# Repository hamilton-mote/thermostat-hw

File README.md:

# Hamilton open-source thermostat

The Hamilton thermostat is an open-source single stage thermostat built around the [Hamilton](https://github.com/hamilton-mote/hw) and [Nucleum](https://github.com/lab11/nucleum) motes. The core motivation of the project is to integrate the hardware necessary to turn these low-cost and low-power motes into an energy efficient and feature-rich thermostat.

The Hamilton thermostat can control a standard single stage heating and/or cooling system with a circular fan (R/Rh/Rc, W, Y, and G wires). The design features a temperature sensor (AT30TS74), humidity/temperature sensor (HDC1080), PIR sensor (EKMB1101111), real-time clock (MCP7940N), and 1Mbit EEPROM (AT24CM01). Wireless communication is achieved via the 802.15.4 radio (built into the SAMR21 of the Hamilton mote) or the Bluetooth Low Energy (BLE) radio (built into the NRF51822 of the Nucleum mote). The thermostat can be powered by 3 AA batteries or by 24VAC power (requires a C wire). The design also includes a simple user interface with 4 buttons and LED-based temperature and setting indication. The user interface can easily be replaced with a custom board by connecting to the main thermostat board via pinouts for the I2C bus, power (+3V3/GND), 2 analog pins, and 4 digital pins.

### Parts Overview

* AT30TS74 (I2C Address 1001000): The AT30TS74 temperature sensor has a configurable resolution of 9 to 12 bits and a typical accuracy of +/- 1 degree Celsius.
* HDC1080 (I2C Address 1000000): The HDC1080 humidity and temperature sensor has a configurable resolution of 8, 11, or 14 bits for humidity and 11 or 14 bit for temperature. The typical accuracy for humidity and temperature is +/- 2% and +/- 0.2 degree Celsius, respectively.
* MCP7940N (I2C Address 1101111): The MCP7940N is a real-time clock/calendar with SRAM.
* AT24CM02 (I2C Address 10100###): The AT24CM02 provides 2-Mbits (256-Kbytes) of Serial EEPROM. (Note: The original version of the Hamilton thermostat included AT24CM01 chips)
* PCA9557 (I2C Address 0011000): The PCA9557 is an 8 channel I/O parallel port expander. The expander is used to control the 3 latching relays (EE2-3TNUH-L) which actuate the heating system, cooling system, and circular fan.
* TLC59116 (I2C Addresses 1100001, 1100011, and 1100111): The TLC59116 is a 16 channel constant-current LED sink driver with 256-step (8-bit) linear programmable brightness. The Hamilton thermostat interface board includes 3 TLC59116 chips.
* EKMB1101111: The EKMB1101111 is a fully integrated PIR motion sensor with 1µA low current consumption. The output of the PIR sensor is connected to pin PA06 of the SAMR21 chip and P05/AIN6 of the NRF51822 chip.

### Communication

Communication between the SAMR21 chip or the NRF51822 chip and the other components of the Hamilton thermostat is primarily achieved via the shared I2C bus. The SAMR21 chip is connected to the bus with pin PA16 as SDA and PA17 as SCL and the NRF51822 chip is connected with pin P07 as SDA and P01 as SCL. The I2C addresses of the components are noted in the list above.

Communication between the SAMR21 chip and the NRF51822 chip is achieved over an SPI link. The SAMR21 chip is design to use SERCOM2 with PA08/PAD[0] as MOSI, PA09/PAD[1] as MISO,
PA15/PAD[3] as SCK, and PA14/PAD[2] as chip select.  The NRF51822 chip provides flexibility in the assignment of SPI pins and is designed to use P30 as MOSI, P29 as MISO, P00 as SCK, and P28 as chip select.

Additionally, the SAMR21 and NRF51822 chips are connected by several additional traces.
* A6 (the PIR sensor output) to SAMR21 pin PA06 and NRF51822 pin P05/AIN6.
* A7 to SAMR21 pin PA07 and NRF51822 pin P06/AIN7.
* D18 to SAMR21 pin PA18 and NRF51822 pin P18.
* D19 to SAMR21 pin PA19 and NRF51822 pin P19. There is also an LED connected to D19.
* D24 to SAMR21 pin PA24 and NRF51822 pin P25.
* D25 to SAMR21 pin PA25 and NRF51822 pin P25.
If necessary, these traces can be physically cut on the bottom on the Hamilton thermostat main board to sever the connections to the NRF51822 chip.

Lastly, the Hamilton thermostat is capable of wireless communication via the 802.15.4 radio (built into the SAMR21 chip) and the BLE radio (built into the NRF51822 chip).

### Relays

The Hamilton thermostat main board includes 3 EE2-3TNUH-L dual-coil latching signal relays for actuating a heating system (W wire), cooling system (Y wire), and circular fan (G wire).  Each relay is rated for a coil voltage of 3VDC, a contact current of 2A, and a switching voltage of up to 250VAC. Because the EE2-3TNUH-L is a latching relay, it maintains the contact position indefinitely without requiring a current to be applied. Thus, each relay contains 2 coils (1 for setting and 1 for releasing) and a current pulse is applied to either coil to change the contact position. Note that applying a current to one of the coils over a long period of time will damage the relay.

Each relay is connected to either the W wire (heat), Y wire (cooling), or G wire (fan). Setting a relay will connect the respective wire to the R/Rh/Rc wire and releasing the relay will sever the connection. The relays are controlled via the PCA9557 8 channel I/O expander. The W relay is connected to IO0 for setting and IO1 for releasing, the Y relay to IO2 for setting and IO3 for releasing, and the G relay to IO4 for setting and IO5 for releasing.

Lastly, the Hamilton thermostat is capable of simultaneously connecting the G wire (fan) when the W relay or Y relay is set. Adding the R18 jumper will cause the W relay to connect both the W and G wires to R when the relay is set and adding the R17 jumper will cause the Y relay to connect the Y and G relays to R.

### Power

The Hamilton thermostat can be power by battery and/or 24VAC power (if a C wire is available). The Hamilton thermostat main board includes a 3 AA battery holder and a AP2210 3.3VDC 300mA LDO regulator. If necessary, regulator can be bypassed by adding the R1 jumper.

If a C wire is available, the thermostat can operate on 24VAC power. For AC/DC conversion, the main board includes a full wave bridge rectifier and an OKI-78SR 36VDC to 3.3VDC 1.5A buck converter. The thermostat is designed to allow for operation on 24VAC power with battery backup.

### User Interface

The Hamilton thermostat has a simple and intuitive user interface for communicating the current temperature measurement and set point and for enabling a user to perform basic operations like setting the mode (heating, cooling, off) and adjusting the set point. The interface board includes four buttons: one for setting the mode, two for adjusting the temperature set point, and one for setting a temporary temperature hold.

The board also includes 40 LEDs for denoting the thermostats settings. To communicate the current temperature measurement and set point, 32 of the LEDs are arranged in an arc around the center of the board (16 for the measurement and 16 for the set point). The LEDs are controlled via three TLC59116 16 channel LED sink drivers.

The interface board is connected to the main thermostat board via pinouts for the I2C bus (SDA and SCL), power (+3.3VDC and GND), analog pins A6 and A7, and digital pins D18, D19, D24, and D25.

### Transient Voltage Suppression (TVS)

To protect the thermostat components from voltage spikes and electrostatic discharge (ESD), the Hamilton thermostat main and interface boards include several transient-voltage-suppression diodes.

On the main board:
* Diode D2 protects the 24VDC output of the diode rectifier and the voltage input of the buck converter.
* Diode D15 protects the batteries and the voltage input of the LDO regulator.
* Diode D16 protects the 3.3V line.
* Integrated diodes U8 (IP4220CZ6) protects the I2C lines.

On the interface board:
* Diodes D41, D42, D43, and D44 protect the output of each button on the interface board.
* Diode D45 protects the 3.3V line.
* Integrated diodes U5 (IP4220CZ6) protects the I2C lines.

### Changelog
* Added IP4220CZ6 diode (U8) to BOM of main board
* Replaced AT24CM01 with AT24CM02 in BOM of main board

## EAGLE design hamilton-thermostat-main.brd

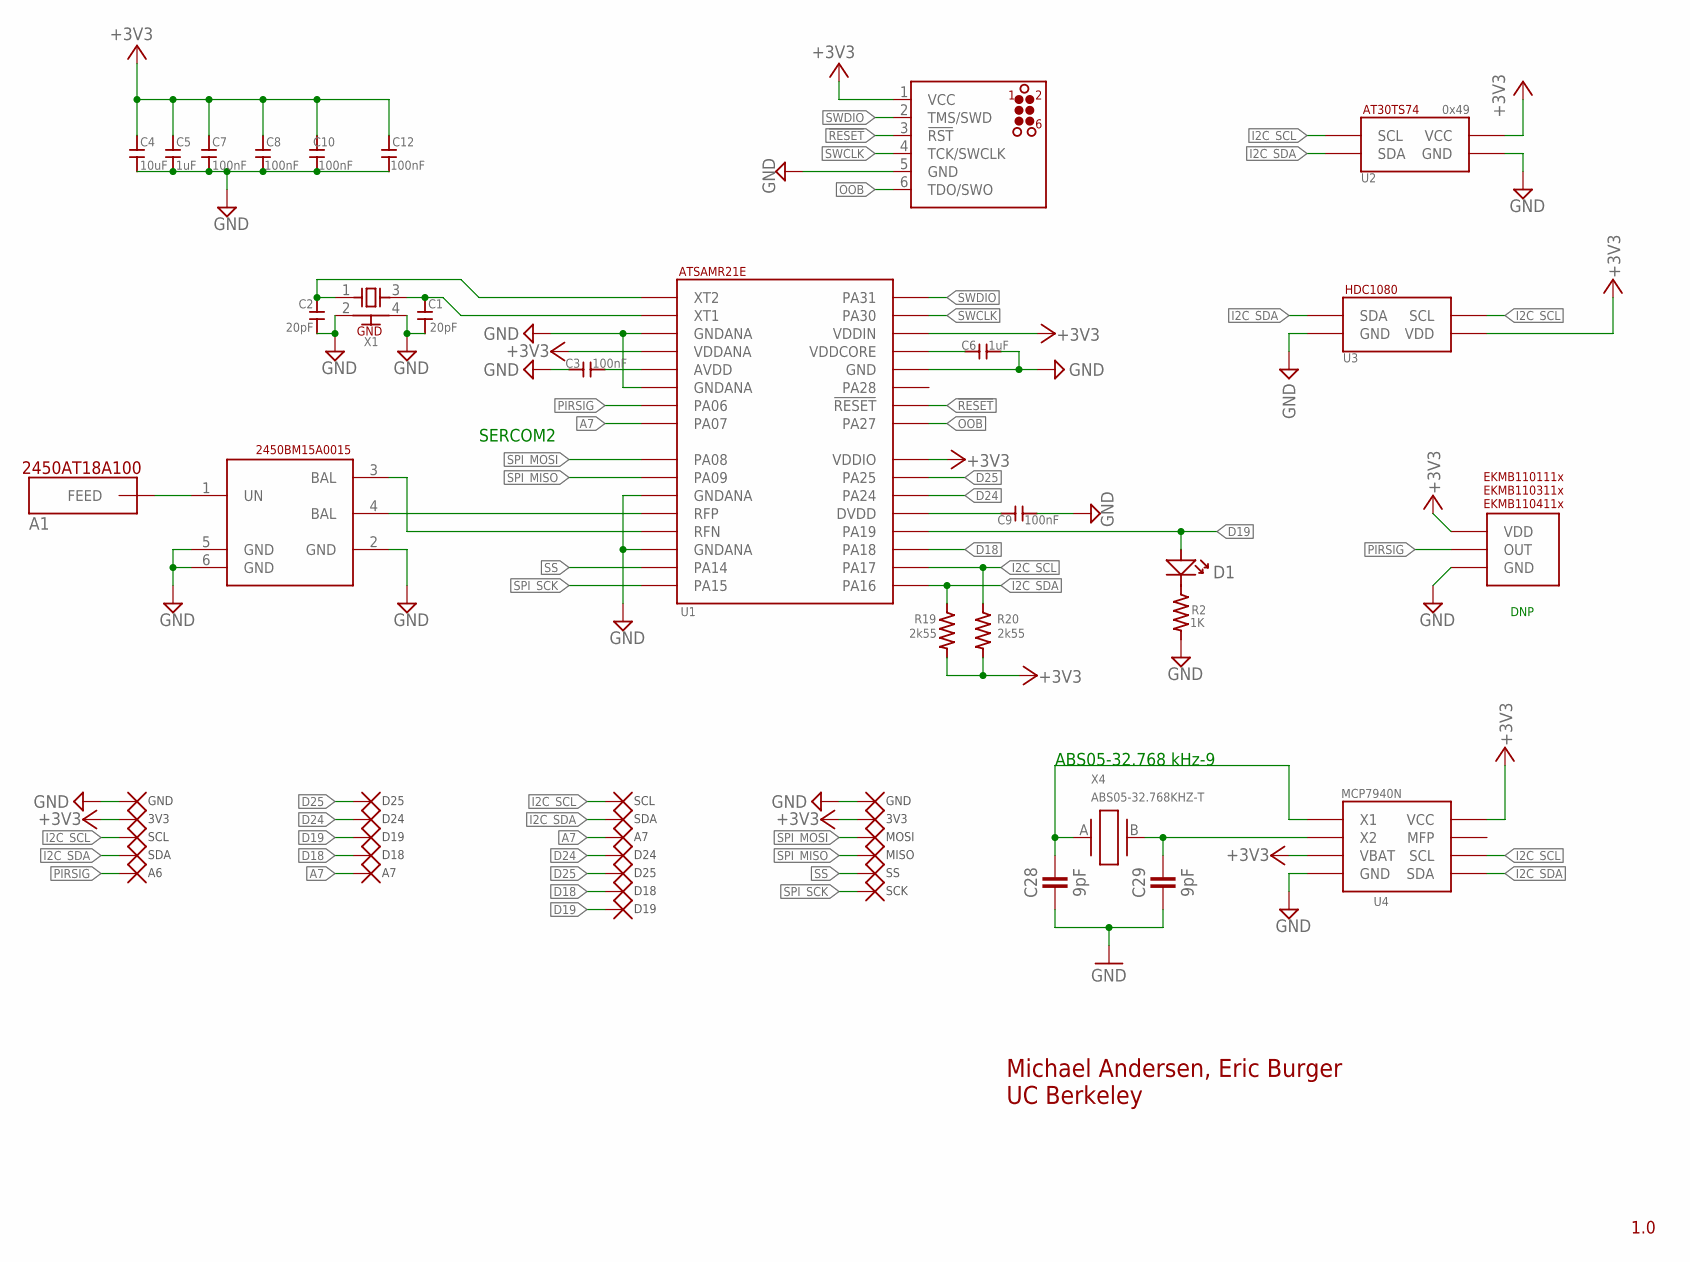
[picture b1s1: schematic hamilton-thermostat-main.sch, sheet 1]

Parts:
A1: JOHANSON_ANTENNA2
C1, C2: 20pF; S0402
C3, C7, C8, C9, C10, C12: 100nF; S0402
C4: 10uF; 0805
C5, C6: 1uF; S0402
C28, C29: 9pF; 0402_CAP
D1: DNP; LINE_0603
L1: BALUN_JOHANSON
R2: 1K; S0402
R19, R20: 2k55; S0402
TP1, TP18: D19; TPP
TP2, TP17: D18; TPP
TP3, TP19: A7; TPP
TP4, TP14: D25; TPP
TP6, TP12: GND; TPP
TP7, TP9: SDA; TPP
TP8, TP10: SCL; TPP
TP11, TP24: 3V3; TPP
TP13, TP15: D24; TPP
TP16: A6; TPP
TP20: MOSI; TPP
TP21: MISO; TPP
TP22: SS; TPP
TP23: SCK; TPP
U1: SAMR21; QFN32
U2: AT30TS74; 4WLCSP
U3: HDC1080; WSON_HDC1080
U4: MCP7940N; SO8
U7: PANASONIC_PIR; PIR
U$1: JLINK_CONNECTWL; TC2030-MCP
X1: XTAL
X4: ABS05-32.768KHZ-T; ABS05

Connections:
!RESET!: U1.26 (!RESET!), U$1.3 (!RST!)
+3V3: C4.2, C5.P$2, C7.P$1, C8.P$1, C10.P$1, C12.P$1, R19.P$1, R20.P$1, TP11.P$1, TP24.P$1, U1.4 (VDDANA), U1.24 (VDDIO), U1.30 (VDDIN), U2.A1 (VCC), U3.5 (VDD), U4.3 (VBAT), U4.8 (VCC), U7.VDD, U$1.1 (VCC); also elsewhere on the board
A7: TP3.P$1, TP19.P$1, U1.8 (PA07); also elsewhere on the board
D18: TP2.P$1, TP17.P$1, U1.19 (PA18); also elsewhere on the board
D19: D1.P (+), TP1.P$1, TP18.P$1, U1.20 (PA19); also elsewhere on the board
D24: TP13.P$1, TP15.P$1, U1.22 (PA24); also elsewhere on the board
D25: TP4.P$1, TP14.P$1, U1.23 (PA25); also elsewhere on the board
GND: C1.P$1, C2.P$1, C3.P$2, C4.1, C5.P$1, C6.P$1, C7.P$2, C8.P$2, C9.P$1, C10.P$2, C12.P$2, C28.2, C29.2, L1.2 (GND), L1.5 (GND), L1.6 (GND), R2.P$1, TP6.P$1, TP12.P$1, U1.3 (GNDANA), U1.6 (GNDANA), U1.11 (GNDANA), U1.14 (GNDANA), U1.28 (GND), U2.A2 (GND), U3.2 (GND), U4.4 (GND), U7.GND, U$1.5 (GND), X1.2 (GND), X1.4 (GND); also elsewhere on the board
I2C_SCL: R20.P$2, TP8.P$1, TP10.P$1, U1.18 (PA17), U2.B2 (SCL), U3.6 (SCL), U4.6 (SCL); also elsewhere on the board
I2C_SDA: R19.P$2, TP7.P$1, TP9.P$1, U1.17 (PA16), U2.B1 (SDA), U3.1 (SDA), U4.5 (SDA); also elsewhere on the board
unnamed: L1.3 (BAL), U1.13 (RFN)
unnamed: A1.FEED, L1.1 (UN)
unnamed: C2.P$2, U1.1 (XT2), X1.1 (X1)
unnamed: C6.P$2, U1.29 (VDDCORE)
unnamed: C3.P$1, U1.5 (AVDD)
unnamed: C1.P$2, U1.2 (XT1), X1.3 (X2)
unnamed: C9.P$2, U1.21 (DVDD)
unnamed: L1.4 (BAL), U1.12 (RFP)
unnamed: D1.N (-), R2.P$2
unnamed: C28.1, U4.1 (X1), X4.A (1)
unnamed: C29.1, U4.2 (X2), X4.B (2)
OOB: U1.25 (PA27), U$1.6 (TDO/SWO)
PIRSIG: TP16.P$1, U1.7 (PA06), U7.OUT; also elsewhere on the board
SPI_MISO: TP21.P$1, U1.10 (PA09); also elsewhere on the board
SPI_MOSI: TP20.P$1, U1.9 (PA08); also elsewhere on the board
SPI_SCK: TP23.P$1, U1.16 (PA15); also elsewhere on the board
SS: TP22.P$1, U1.15 (PA14); also elsewhere on the board
SWCLK: U1.31 (PA30), U$1.4 (TCK/SWCLK)
SWDIO: U1.32 (PA31), U$1.2 (TMS/SWD)

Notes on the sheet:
1.0
Michael Andersen, Eric Burger UC Berkeley
0x49
SERCOM2
ABS05-32.768 kHz-9
DNP

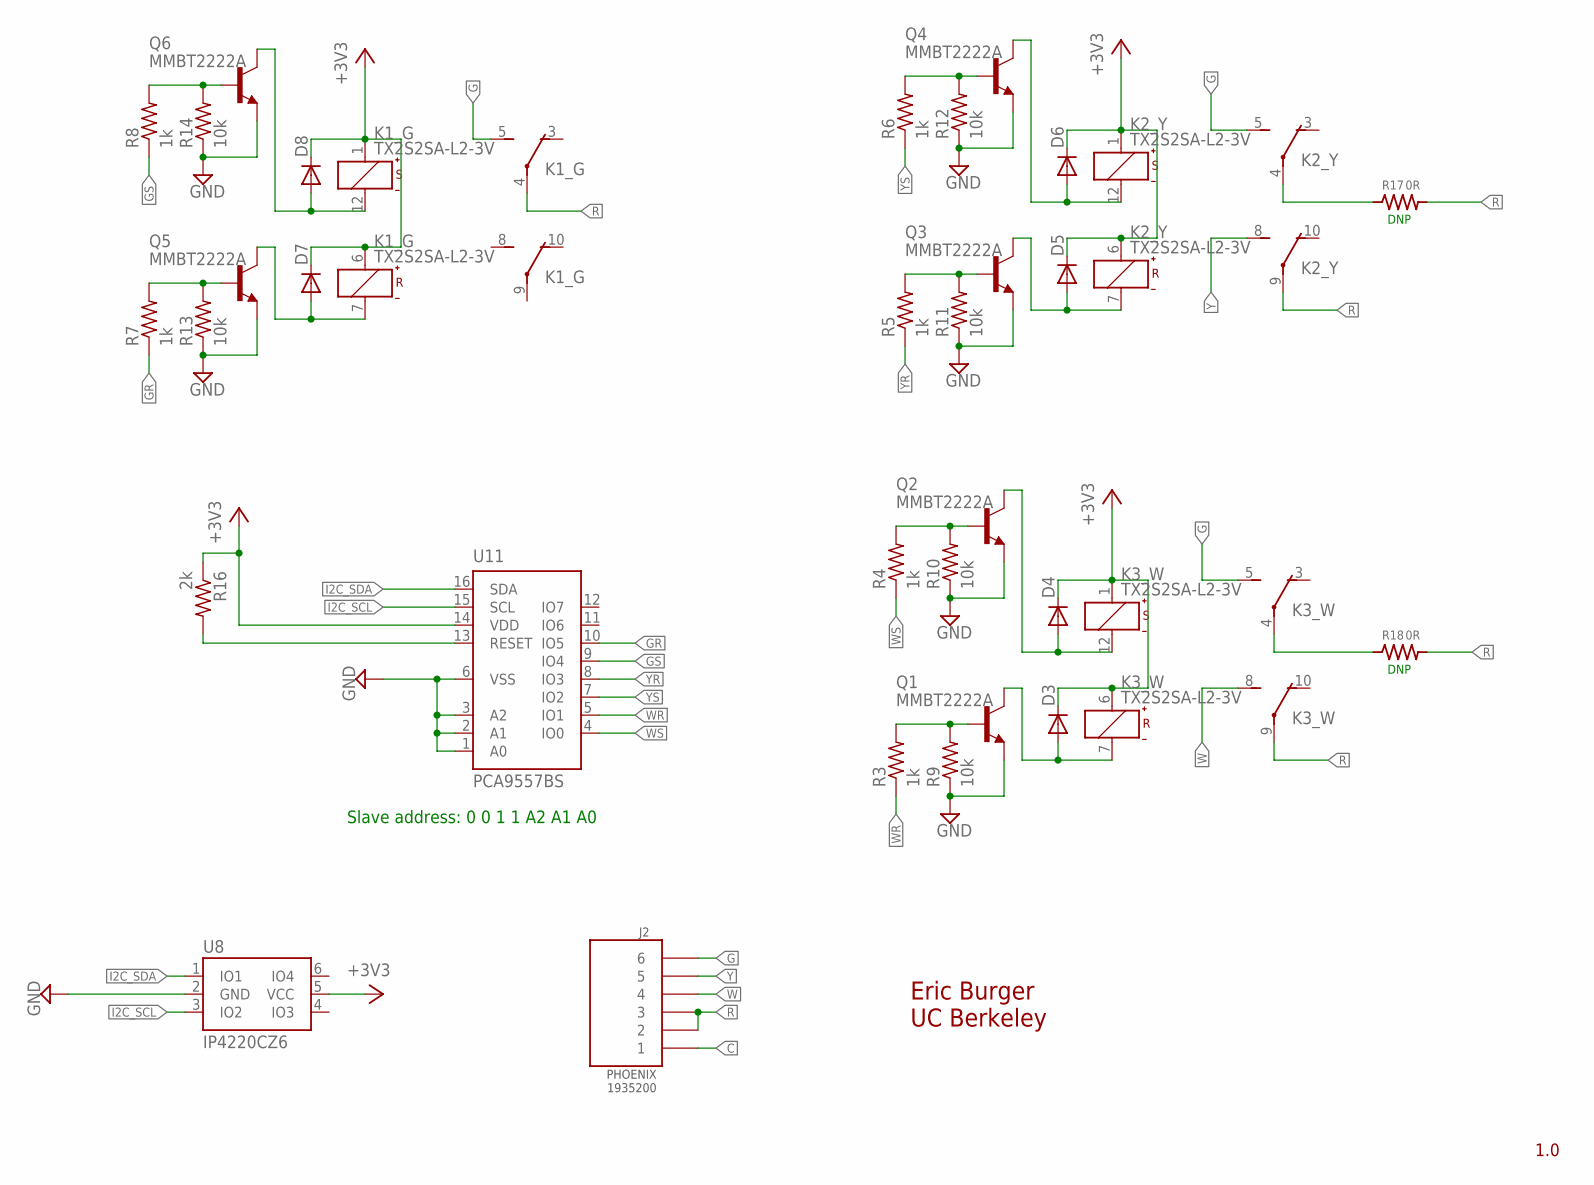
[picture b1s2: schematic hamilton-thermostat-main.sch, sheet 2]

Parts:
D3, D4, D5, D6, D7, D8: DIODE-DO-214AC; DO-214AC
J2: PHOENIX6W5MM
K1_G, K2_Y, K3_W: TX2S2SA-L2-3V; TX2SA-L2
Q1, Q2, Q3, Q4, Q5, Q6: MMBT2222A; SOT23-3
R3, R4, R5, R6, R7, R8: 1k; R0402
R9, R10, R11, R12, R13, R14: 10k; R0402
R16: 2k; R0402
R17, R18: 0R; S0402
U8: IP4220CZ6; SOT23-6
U11: PCA9557BS; HVQFN16_4X4

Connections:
+3V3: D3.C, D4.C, D5.C, D6.C, D7.C, D8.C, K1_G.1 (+), K1_G.6 (+), K2_Y.1 (+), K2_Y.6 (+), K3_W.1 (+), K3_W.6 (+), R16.1, U8.5 (VCC), U11.14 (VDD); also elsewhere on the board
C: J2.P$1 (1); also elsewhere on the board
G: J2.P$6 (6), K1_G.5 (S), K2_Y.5 (S), K3_W.5 (S)
GND: Q1.2 (E), Q2.2 (E), Q3.2 (E), Q4.2 (E), Q5.2 (E), Q6.2 (E), R9.1, R10.1, R11.1, R12.1, R13.1, R14.1, U8.2 (GND), U11.1 (A0), U11.2 (A1), U11.3 (A2), U11.6 (VSS); also elsewhere on the board
GR: R7.1, U11.10 (IO5)
GS: R8.1, U11.9 (IO4)
I2C_SCL: U8.3 (IO2), U11.15 (SCL); also elsewhere on the board
I2C_SDA: U8.1 (IO1), U11.16 (SDA); also elsewhere on the board
unnamed: Q2.1 (B), R4.2, R10.2
unnamed: R16.2, U11.13 (RESET)
unnamed: D3.A, K3_W.7 (-), Q1.3 (C)
unnamed: D4.A, K3_W.12 (-), Q2.3 (C)
unnamed: Q4.1 (B), R6.2, R12.2
unnamed: Q1.1 (B), R3.2, R9.2
unnamed: D5.A, K2_Y.7 (-), Q3.3 (C)
unnamed: Q3.1 (B), R5.2, R11.2
unnamed: D6.A, K2_Y.12 (-), Q4.3 (C)
unnamed: Q6.1 (B), R8.2, R14.2
unnamed: D7.A, K1_G.7 (-), Q5.3 (C)
unnamed: Q5.1 (B), R7.2, R13.2
unnamed: D8.A, K1_G.12 (-), Q6.3 (C)
unnamed: K2_Y.4, R17.P$2
unnamed: K3_W.4, R18.P$2
R: J2.P$2 (2), J2.P$3 (3), K1_G.4, K2_Y.9, K3_W.9, R17.P$1, R18.P$1; also elsewhere on the board
W: J2.P$4 (4), K3_W.8 (S)
WR: R3.1, U11.5 (IO1)
WS: R4.1, U11.4 (IO0)
Y: J2.P$5 (5), K2_Y.8 (S)
YR: R5.1, U11.8 (IO3)
YS: R6.1, U11.7 (IO2)

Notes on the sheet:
1.0
Eric Burger UC Berkeley
Slave address: 0 0 1 1 A2 A1 A0
DNP

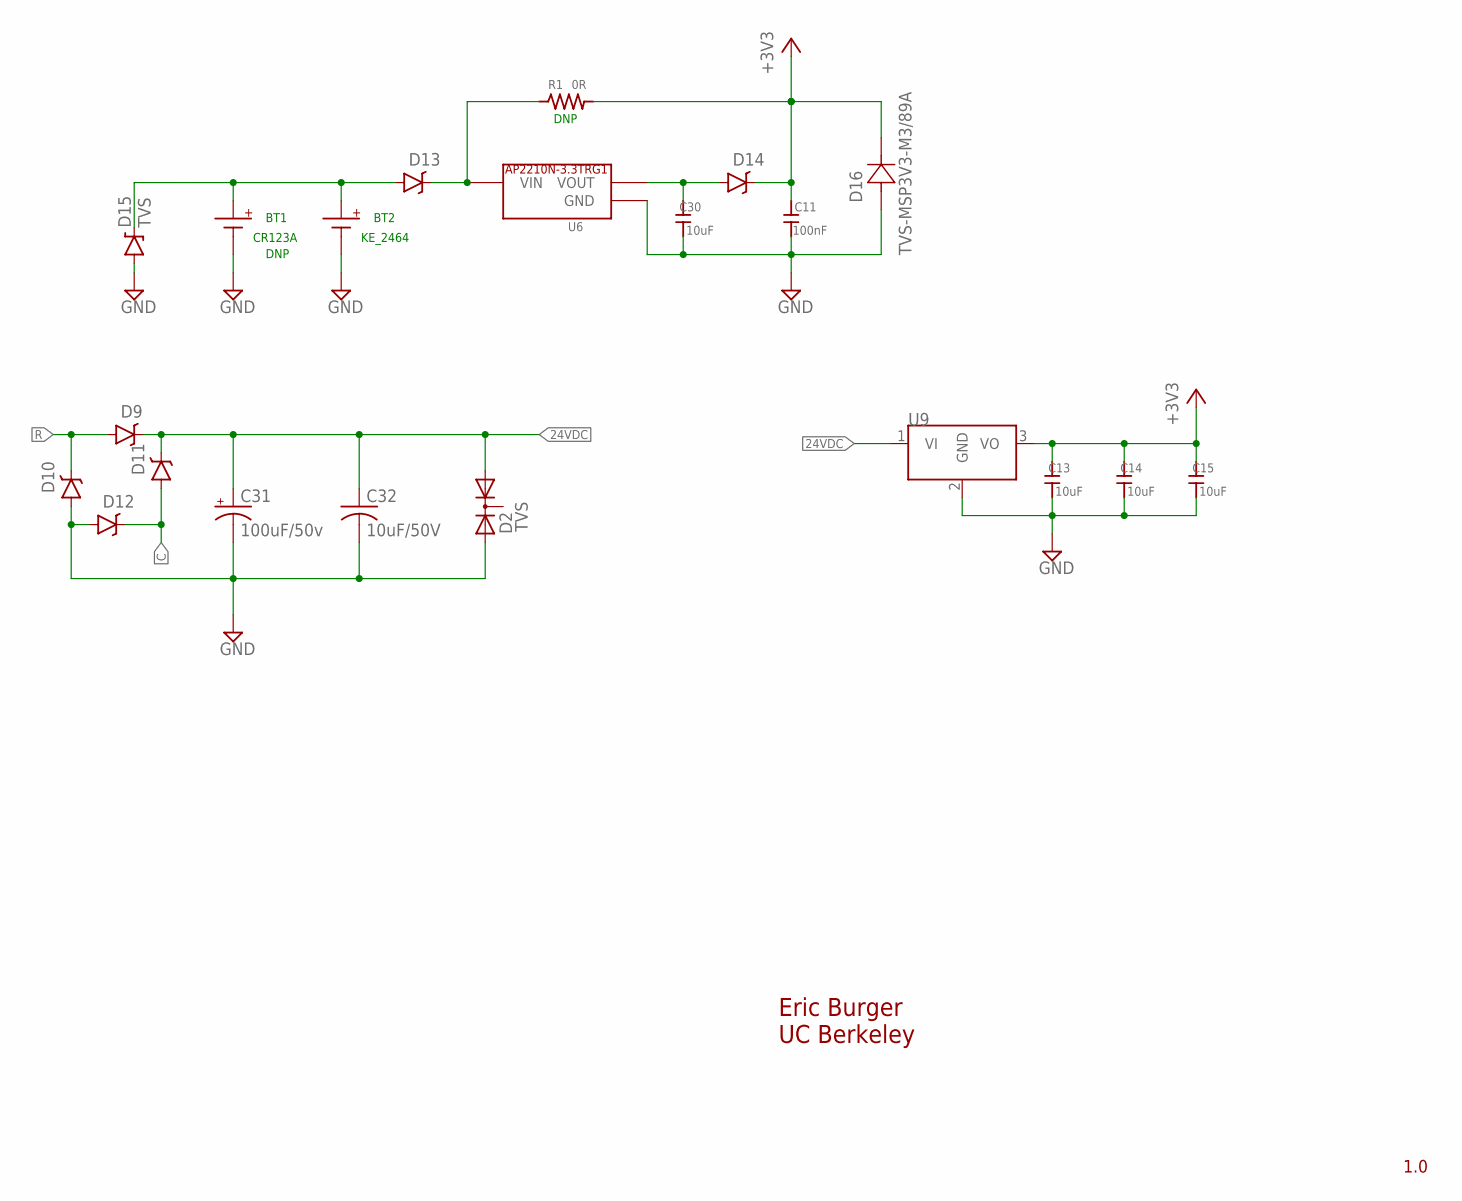
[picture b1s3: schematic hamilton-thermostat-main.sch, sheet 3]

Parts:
BT1: CR123A
BT2: BATTERY; KE_2464
C11: 100nF; S0402
C13, C14, C15, C30: 10uF; 0805
C31: 100uF/50v; NIC_10X10.5_CAP
C32: 10uF/50V; C1206
D2: TVS; SOT23
D9, D10, D11, D12, D13, D14: MBRA140; SMA-DIODE
D15: TVS; SMB-DIODE
D16: TVS-MSP3V3-M3/89A; DIODE_MSP3V3
R1: 0R; S0402
U6: SOT23-3VREG; SOT23
U9: DCDC_OKI-78SR; OKI-78SRH

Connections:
24VDC: C31.+, C32.1, D2.1 (A1), D9.C, D11.C, U9.1 (VI)
+3V3: C11.P$1, C13.2, C14.2, C15.2, D14.C, D16.1 (12), R1.P$1, U9.3 (VO); also elsewhere on the board
C: D11.A, D12.C; also elsewhere on the board
GND: BT1.NEG (-), BT2.NEG (-), C11.P$2, C13.1, C14.1, C15.1, C30.1, C31.-, C32.2, D2.2 (A2), D10.A, D12.A, D15.A, D16.2 (21), U6.1 (GND), U9.2 (GND); also elsewhere on the board
unnamed: C30.2, D14.A, U6.2 (VOUT)
unnamed: D13.C, R1.P$2, U6.3 (VIN)
unnamed: BT1.POS (+), BT2.POS (+), D13.A, D15.C
R: D9.A, D10.C; also elsewhere on the board

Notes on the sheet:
1.0
Eric Burger UC Berkeley
CR123A
DNP
KE_2464
BT1
BT2

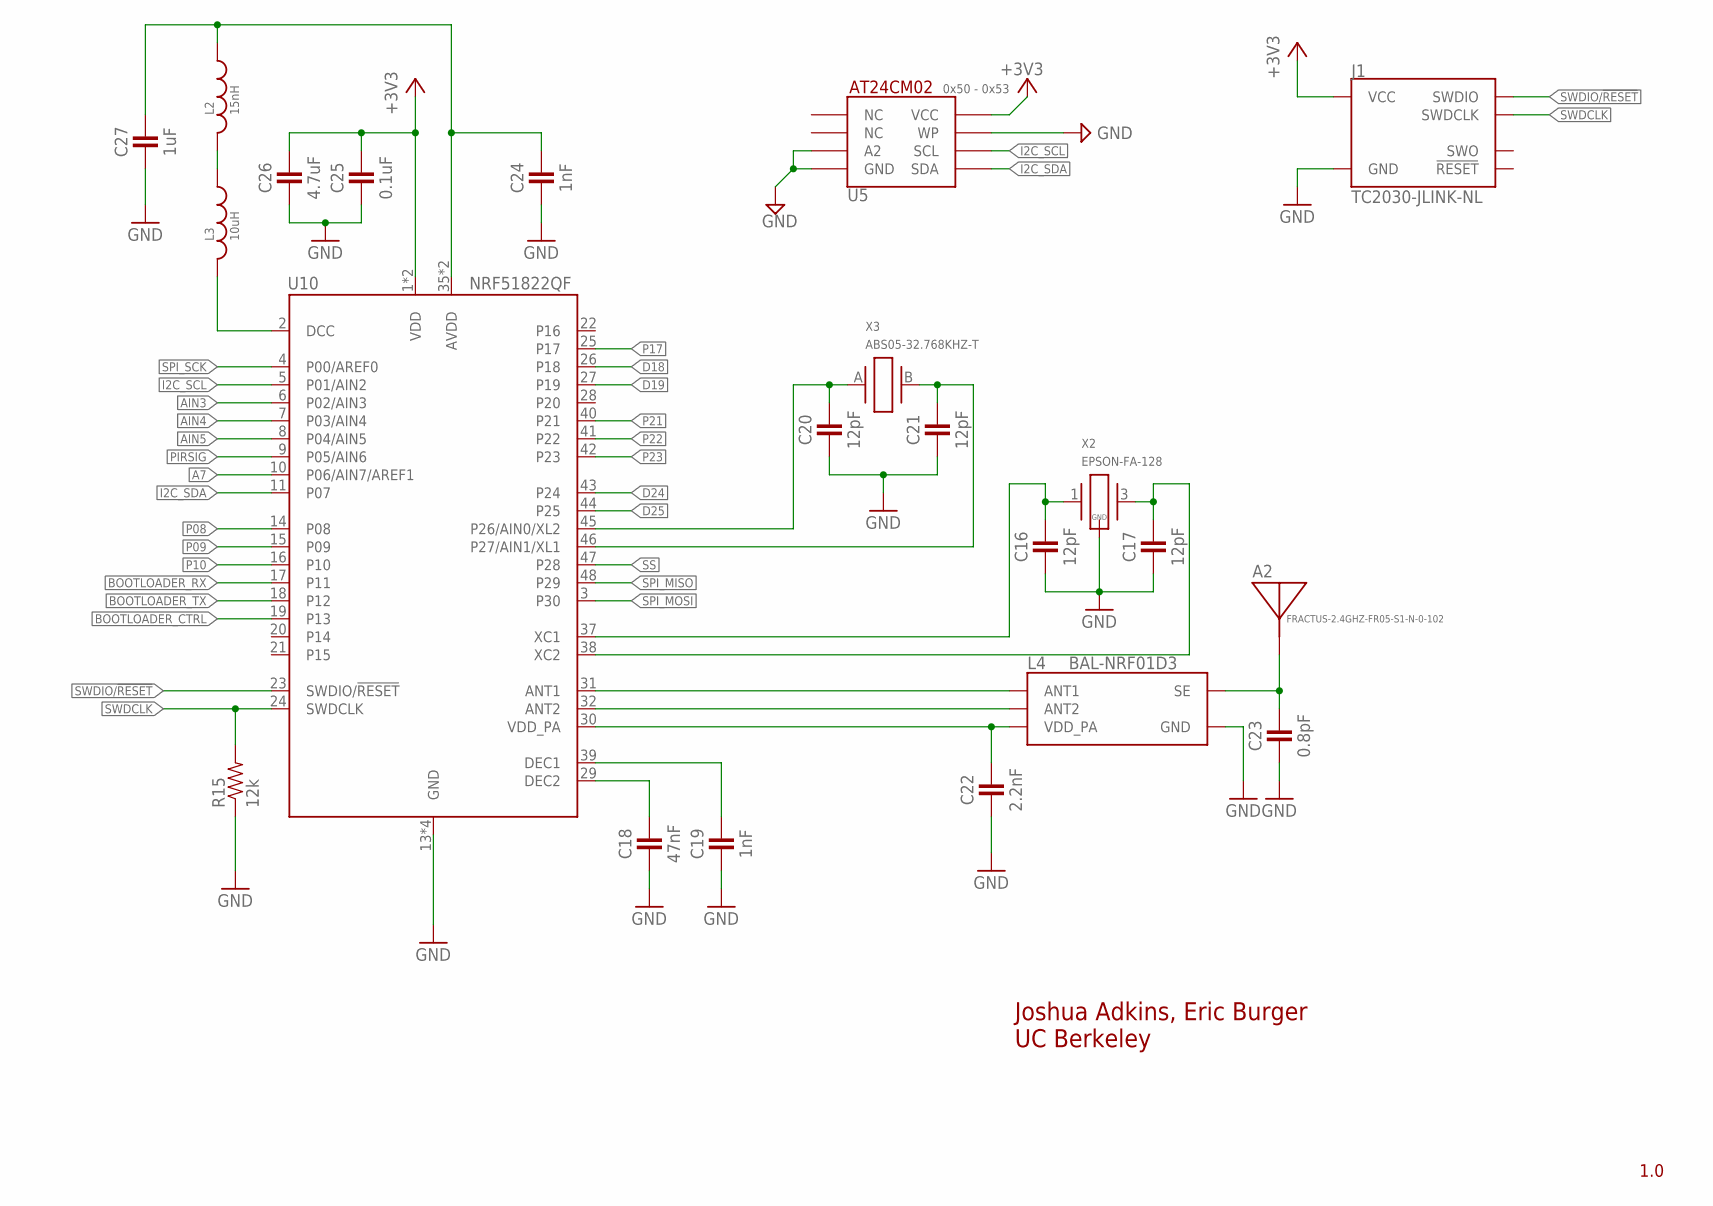
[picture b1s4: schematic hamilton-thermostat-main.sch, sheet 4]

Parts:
A2: FRACTUS-2.4GHZ-FR05-S1-N-0-102; FRACTUS-ANTENNA-FR05-S1-N-0-102
C16, C17, C20, C21: 12pF; 0402_CAP
C18: 47nF; 0402_CAP
C19, C24: 1nF; 0402_CAP
C22: 2.2nF; 0402_CAP
C23: 0.8pF; 0402_CAP
C25: 0.1uF; 0402_CAP
C26: 4.7uF; 0402_CAP
C27: 1uF; 0402_CAP
J1: TC2030-JLINK-NL; TC2030-IDC-NL
L2: 15nH; 0402_CAP
L3: 10uH; 0603_CAP
L4: BAL-NRF01D3
R15: 12k; 0402_RES
U5: AT24CM02; SO8
U10: NRF51822QF; QFN-48-6MM
X2: EPSON-FA-128; FA-128
X3: ABS05-32.768KHZ-T; ABS05

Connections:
+3V3: C25.1, C26.1, J1.1 (VCC), U5.8 (VCC), U10.1 (VDD), U10.12 (VDD); also elsewhere on the board
A7: U10.10 (P06/AIN7/AREF1); also elsewhere on the board
AIN3: U10.6 (P02/AIN3)
AIN4: U10.7 (P03/AIN4)
AIN5: U10.8 (P04/AIN5)
ANTENNA: A2.1, C23.1, L4.SE
BOOTLOADER_CTRL: U10.19 (P13)
BOOTLOADER_RX: U10.17 (P11)
BOOTLOADER_TX: U10.18 (P12)
D18: U10.26 (P18); also elsewhere on the board
D19: U10.27 (P19); also elsewhere on the board
D24: U10.43 (P24); also elsewhere on the board
D25: U10.44 (P25); also elsewhere on the board
GND: C16.2, C17.2, C18.2, C19.2, C20.2, C21.2, C22.2, C23.2, C24.2, C25.2, C26.2, C27.2, J1.5 (GND), L4.GND, R15.1, U5.3 (A2), U5.4 (GND), U5.7 (WP), U10.13 (GND), U10.33 (GND), U10.34 (GND), U10.GND, X2.2 (GND), X2.4 (GND); also elsewhere on the board
I2C_SCL: U5.6 (SCL), U10.5 (P01/AIN2); also elsewhere on the board
I2C_SDA: U5.5 (SDA), U10.11 (P07); also elsewhere on the board
unnamed: C16.1, U10.37 (XC1), X2.1
unnamed: C17.1, U10.38 (XC2), X2.3 (2)
unnamed: C18.1, U10.29 (DEC2)
unnamed: C20.1, U10.45 (P26/AIN0/XL2), X3.A (1)
unnamed: C21.1, U10.46 (P27/AIN1/XL1), X3.B (2)
unnamed: C19.1, U10.39 (DEC1)
unnamed: L4.ANT1, U10.31 (ANT1)
unnamed: L4.ANT2, U10.32 (ANT2)
unnamed: C22.1, L4.VCC (VDD_PA), U10.30 (VDD_PA)
unnamed: C24.1, C27.1, L2.1, U10.35 (AVDD), U10.36 (AVDD)
unnamed: L2.2, L3.1
unnamed: L3.2, U10.2 (DCC)
P08: U10.14 (P08)
P09: U10.15 (P09)
P10: U10.16 (P10)
P17: U10.25 (P17)
P21: U10.40 (P21)
P22: U10.41 (P22)
P23: U10.42 (P23)
PIRSIG: U10.9 (P05/AIN6); also elsewhere on the board
SPI_MISO: U10.48 (P29); also elsewhere on the board
SPI_MOSI: U10.3 (P30); also elsewhere on the board
SPI_SCK: U10.4 (P00/AREF0); also elsewhere on the board
SS: U10.47 (P28); also elsewhere on the board
SWDCLK: J1.4 (SWDCLK), R15.2, U10.24 (SWDCLK)
SWDIO/!RESET: J1.2 (SWDIO), U10.23 (SWDIO/!RESET)

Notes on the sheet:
Joshua Adkins, Eric Burger UC Berkeley
1.0
0x50 - 0x53

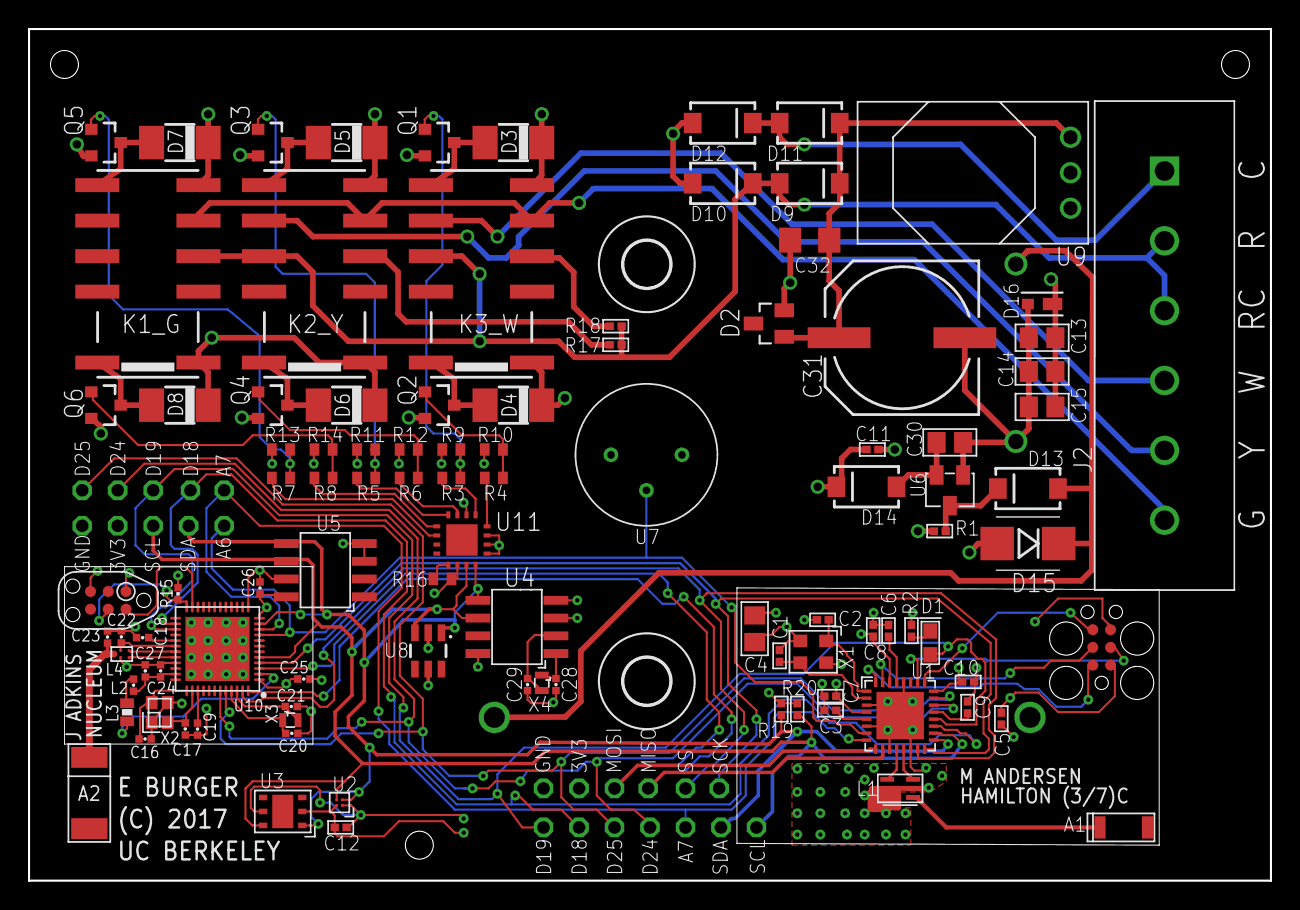
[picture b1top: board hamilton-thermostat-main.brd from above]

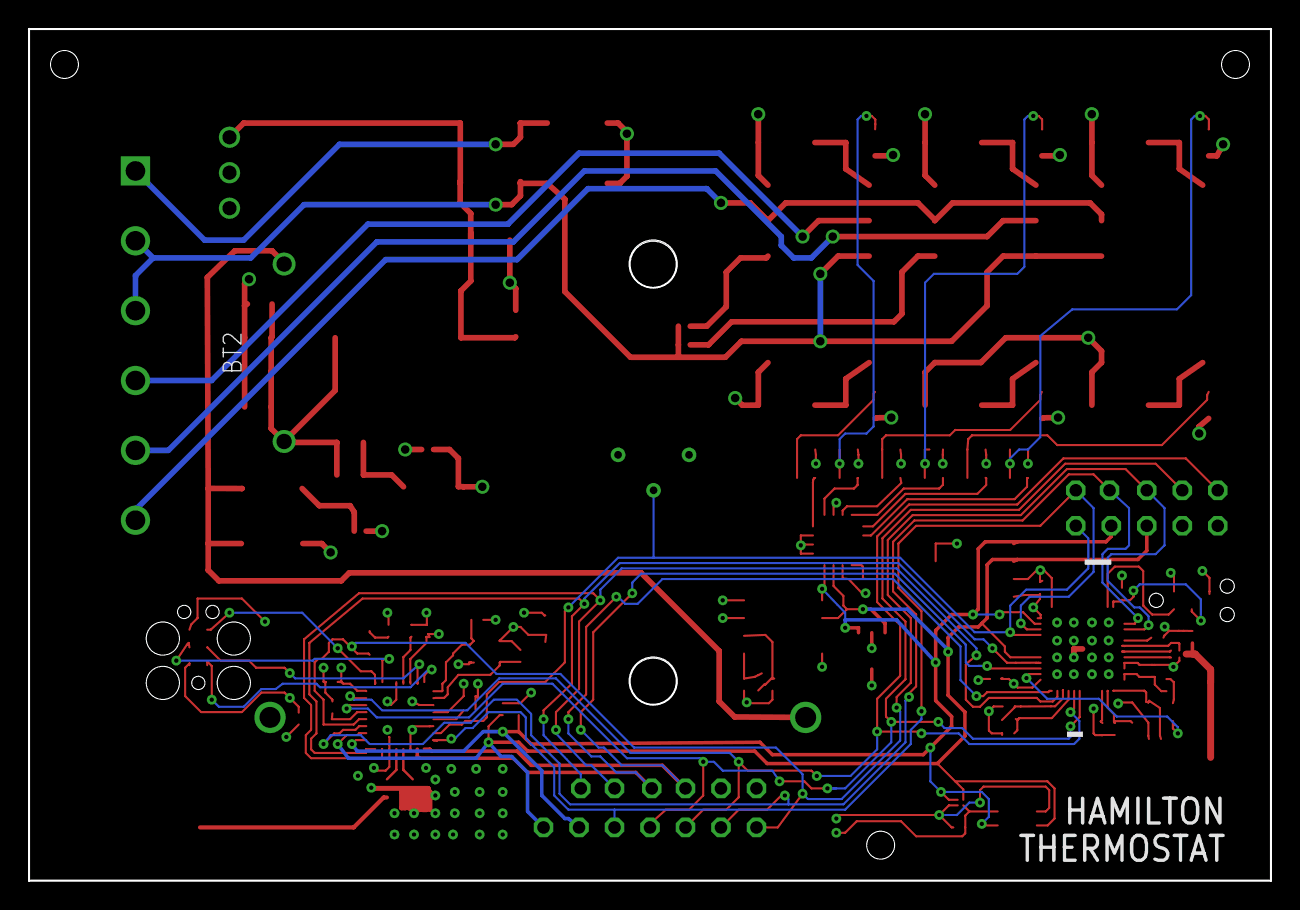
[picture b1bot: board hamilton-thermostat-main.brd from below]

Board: 4 copper layers, 88.9 x 61.0 mm, 128 parts (2 on the bottom side), 74 nets.

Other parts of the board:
U$3, U$4: 3,3

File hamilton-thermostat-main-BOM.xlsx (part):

Name(s) | Part | Digikey Part | Description | Package | Price @ 5000 | Price @ 1 | Quantity Per | Links
A1 | 2450AT18A100E | 712-1005-1-ND | antenna |  | 0.2175 | 0.62 | 1 | http://www.digikey.com/product-detail/en/2450AT18A100E/712-1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
A2 | FRACTUS-2.4GHZ-FR05-S1-N-0-102 |  | Fractus Compact Reach XtendTM chip antenna |  | 1.1100000000000001 | 1.1100000000000001 | 1 | http://www.richardsonrfpd.com/Pages/Product-Details.aspx?pro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
K1_W, K2_Y, K3_G | EE2-3TNUH-L | 399-11010-2-ND | Dual Coil Latching Relay (2A, 3V Coil) | DPDT (2 Form C) | 1.6379999999999999 | 2.75 | 3 | http://www.digikey.com/product-detail/en/kemet/EE2-3TNUH-L/3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 | http://www.digikey.com/products/en/relays/signal-relays-up-t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
D1 | SML-D12V1WT86 | SML-D12V1WT86CT-ND | led | 0603 (1608 Metric) | 3.5650000000000001E-2 | 0.22 | 1 | http://www.digikey.com/product-detail/en/rohm-semiconductor/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
D3, D4, D5, D6, D7, D8 | GS1A-LTP | GS1A-LTPMSCT-ND | Diode | DO-214AC | 0.04 | 0.28000000000000003 | 6 | http://www.digikey.com/product-detail/en/micro-commercial-co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 | http://www.digikey.com/product-search/en?keywords=Micro%20Co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
D9, D10, D11, D12, D13, D14 | SS2150-LTP | SS2150-LTPMSTR-ND | Schottky Diode (60V 2A) | DO-214AC | 8.8400000000000006E-2 | 0.43 | 4 |  | http://www.digikey.com/products/en/discrete-semiconductor-pr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
D2 | SDC36C.TCT | SDC36CTCTTR-ND | 33V TVS Diode | SOT-23-3 | 0.66473000000000004 | 1.59 | 1 | http://www.digikey.com/product-detail/en/semtech-corporation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
D15 | SMAJ11A | SMAJ11ALFTR-ND | 11V TVS Diode | DO-214AC, SMA | 0.10098 | 0.4 | 1 | http://www.digikey.com/product-detail/en/littelfuse-inc/SMAJ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
D16 | MSP3V3-M3/89A | MSP3V3-M3/89AGITR-ND | 3V3 TVS Diode | MicroSMP | 6.6699999999999995E-2 | 0.39 | 1 | http://www.digikey.com/product-detail/en/stmicroelectronics/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
Q1, Q2, Q3, Q4, Q5, Q6 | MMBT2222ALT1G | MMBT2222ALT1GOSCT-ND | NPN Transistor | TO-236-3 | 1.7469999999999999E-2 | 0.1 | 6 | http://www.digikey.com/product-detail/en/on-semiconductor/MM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 | http://www.digikey.com/product-search/en?keywords=MMBT2222a
U1 | ATSAMR21E18A-MU or ATSAMR21E19A-MFTCT-ND | ATSAMR21E18A-MUTCT-ND | MCU | 32-VFQFN Exposed Pad | 4.2359999999999998 | 4.6399999999999997 | 1 | http://www.digikey.com/product-detail/en/ATSAMR21E18A-MU/ATS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
U2 | AT30TS74 | AT30TS74-U1FMAB-TTR-ND | Temp sensor | 5-WFBGA, WLCSP | 0.54074999999999995 | 0.68 | 1 | http://www.digikey.com/product-detail/en/microchip-technolog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
U3 | HDC1080DMBR | 296-43864-2-ND | Temp sensor |  | 1.35 | 4.6500000000000004 | 1 | http://www.digikey.com/product-detail/en/texas-instruments/H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
U4 | MCP7940N | MCP7940N-I/SN-ND | I2C RTC | 8-SOIC | 0.66949999999999998 | 0.76 | 1 | http://www.digikey.com/product-detail/en/microchip-technolog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
U5 | AT24CM02 | AT24CM02-SSHD-B-ND | 2Mbit EEPROM | 8-SOIC | 1.41831 | 2.2000000000000002 | 1 | https://www.digikey.com/product-detail/en/microchip-technolo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
U6 | AP2210N-3.3TRG1 | AP2210N-3.3TRG1DITR-ND | IC REG LDO 3.3V 0.3A SOT23 | SOT-23-3 | 9.0719999999999995E-2 | 0.42 | 1 | http://www.digikey.com/product-detail/en/diodes-incorporated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
U8 | IP4220CZ6,125 | 1727-3578-1-ND | ESD PROTECTION | SC-74, SOT-457 | 0.12128 | 0.44 | 1 | https://www.digikey.com/product-detail/en/nexperia-usa-inc/I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,125/1727-3…
U10 | NRF51822QF | 1490-1040-1-ND | BLE/2.4 GHz RF SoC | 48-VFQFN Exposed Pad | 2.7048000000000001 | 5.41 | 1 | http://www.digikey.com/products/en?keywords=1490-1040-1-ND
U11 | PCA9557BS,118 | 568-3398-1-ND | I/O EXPANDER I2C 8B | 16-HVQFN | 0.63963000000000003 | 1.41 | 1 | http://www.digikey.com/product-detail/en/nxp-usa-inc/PCA9557BS,118/568-3398-1-N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 | http://www.digikey.com/products/en?keywords=pca9557bs
X1 | 7S-16.000MAHE-T | 887-1833-1-ND | xtal | 4-SMD | 0.50749999999999995 | 1 | 1 | http://www.digikey.com/product-search/en?keywords=887-1833-1-ND
X2 | TXC-8Y | 887-2003-1-ND | CRYSTAL 16MHZ 8PF SMD | 4-SMD | 0.495 | 0.86 | 1 | http://www.digikey.com/products/en?keywords=887-2003-1-ND
X3 | ABS05-32.768KHZ-T | 535-11899-1-ND | 32.768kHz Crystal | 2-SMD | 0.64515 | 1.1200000000000001 | 1 | http://www.digikey.com/products/en?keywords=535-11899-1-ND
X4 | ABS05-32.768KHZ-9-T | 535-11897-2-ND | 32.768kHz Crystal (9 pF) | 2-SMD | 0.56694999999999995 | 1.1200000000000001 | 1 | http://www.digikey.com/product-detail/en/abracon-llc/ABS05-3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
L1 | 2450BM15A0015E | 712-1576-1-ND | balun | 0805 (2012 Metric) | 0.41344999999999998 | 0.96 | 1 | http://www.digikey.com/product-detail/en/2450BM15A0015E/712-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
L2 | INDUCTOR0402 | 587-1521-1-ND | 15nH 0402_IND | 0402 (1005 Metric) | 2.2849999999999999E-2 | 0.1 | 1 | http://www.digikey.com/products/en?keywords=587-1521-1-ND
L3 | INDUCTOR0603 | 490-4025-1-ND | 10uH 0603_IND | 0603 (1608 Metric) | 6.7339999999999997E-2 | 0.14000000000000001 | 1 | http://www.digikey.com/products/en?keywords=490-4025-1-ND
L4 | BAL-NRF01D3 | 497-13637-1-ND | 50 ohm nominal match balun to nRF51422-QFAA, | 5-WFBGA, FCBGA | 0.3296 | 0.77 | 1 | http://www.digikey.com/products/en?keywords=497-13637-1-ND
C16, C17, C20, C21 | 0402 Capacitor | 399-1013-2-ND | 12pF 0402_CAP | 0402 (1005 Metric) | 6.1500000000000001E-3 | 0.1 | 4 | http://www.digikey.com/product-detail/en/kemet/C0402C120J5GA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
C18 | 0402 Capacitor | 445-8093-2-ND | 47nF 0402_CAP | 0402 (1005 Metric) | 2.545E-2 | 0.18 | 1 | http://www.digikey.com/product-detail/en/tdk-corporation/CGJ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
C22 | 0402 Capacitor | 399-13404-2-ND | 2.2nF 0402_CAP | 0402 (1005 Metric) | 2.1819999999999999E-2 | 0.16 | 1 | http://www.digikey.com/product-detail/en/kemet/C0402C222J8JA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
C23 | 0402 Capacitor | 1284-1093-2-ND | 0.8pF 0402_CAP | 0402 (1005 Metric) | 0.40365000000000001 | 1.27 | 1 | http://www.digikey.com/products/en?keywords=1284-1093-2-ND
C26 | 0402 Capacitor | 490-5915-2-ND | 4.7uF 0402_CAP | 0402 (1005 Metric) | 1.9189999999999999E-2 | 0.14000000000000001 | 1 | http://www.digikey.com/product-detail/en/murata-electronics-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
C28, C29 | GRM1555C1H9R0CA01D | 490-8232-2-ND | 9pF 0402_CAP | 0402 (1005 Metric) | 6.1500000000000001E-3 | 0.1 | 2 | http://www.digikey.com/product-detail/en/murata-electronics-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
C31 | UWT1H101MNL1GS | 493-2226-2-ND | 100 uF Alum Cap (50V) | Radial, Can | 0.11475 | 0.15 | 1 |  | http://www.digikey.com/product-detail/en/nichicon/UWT1H101MN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
C32 | UMK316BBJ106ML-T | 587-3248-1-ND | 10 uF Cer Cap (50V) | 1206 (3216 Metric) | 0.10659 | 0.12 | 1 |  | http://www.digikey.com/product-detail/en/taiyo-yuden/UMK316B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
R15 | 0402 Resistor | RHM12.0KCDCT-ND | 12k 0402_RES | 0402 (1005 Metric) | 3.3999999999999998E-3 | 0.1 | 1 | http://www.digikey.com/products/en?keywords=RHM12.0KCDCT-ND
U9 | OKI-78SR-3.3/1.5-W36-C | 811-2195-5-ND | DC/DC 4.95W 36VIN 3.3VOUT | 3-SIP Module | 4.3 | 3.60432 | 1 | http://www.digikey.com/product-detail/en/murata-power-soluti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 | http://www.digikey.com/products/en/power-supplies-board-moun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
J2 | 1935200 | 277-1581-ND | 6POS Screw Terminal | N/A | 0.82450000000000001 | 1.1200000000000001 | 1 | http://www.digikey.com/product-detail/en/phoenix-contact/193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
BT2 (back of board) | Keystone Electronics 2464 | 36-2464-ND | Battery Holder 3 AA | N/A | 0.67430999999999996 | 2.02 | 1 | http://www.digikey.com/product-detail/en/keystone-electronic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
Passives, any brand is ok:
C1, C2 | 20pF 0402 6v3 NP0 / C0G |  |  |  | 3.3899999999999998E-3 | 0.1 | 2
C3, C7, C8, C9, C10, C11, C12, C25 | 100nF 0402 6v3 X5R |  |  |  | 2.16E-3 | 0.1 | 7
C4, C13, C14, C15, C30 | 10uF 0805 6v3 X5R |  |  |  | 5.7499999999999999E-3 | 0.1 | 4
C5, C6, C27 | 1uF 0402 6v3 X5R |  |  |  | 1.91E-3 | 0.1 | 2
C19, C24 | 1nF 0402_CAP |  |  |  | 2.9170000000000001E-2 | 0.19 | 2 | http://www.digikey.com/product-detail/en/kemet/C0402C102J5JA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
R2, R3, R4, R5, R6, R7, R8 | 1K 0402 5% |  |  |  | 1.2099999999999999E-3 | 0.1 | 7
R9, R10, R11, R12, R13, R14 | 10k 0402 5% |  |  |  | 1.2099999999999999E-3 | 0.1 | 6 | http://www.digikey.com/product-detail/en/yageo/RC0402JR-0710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 | http://www.digikey.com/product-search/en/resistors/chip-resi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
R16, R19, R20 | 2k55 0402 5% |  |  |  | 1.2199999999999999E-3 | 0.1 | 2 | http://www.digikey.com/product-detail/en/yageo/RC0402FR-072K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

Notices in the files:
hamilton-thermostat-interface.brd:
(C) 2017
parts and their libraries:
storm: ©2009 ROFA.cz
SparkFun-DiscreteSemi: Licensing: Creative Commons ShareAlike 4.0 International - https://creativecommons.org/licenses/by-sa/4.0
